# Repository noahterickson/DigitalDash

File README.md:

# DigitalDash

The digital dashboard project was completed by a group of students at Portland State University for the Electrical and Computer Engineering Capstone program on behalf of the Viking Motorsports team.

The digital dashboard is intended for a Formula SAE electric vehicle and functions as a visual display of information for various systems on the vehicle.

[Check out our wiki](https://github.com/noahterickson/DigitalDash/wiki)

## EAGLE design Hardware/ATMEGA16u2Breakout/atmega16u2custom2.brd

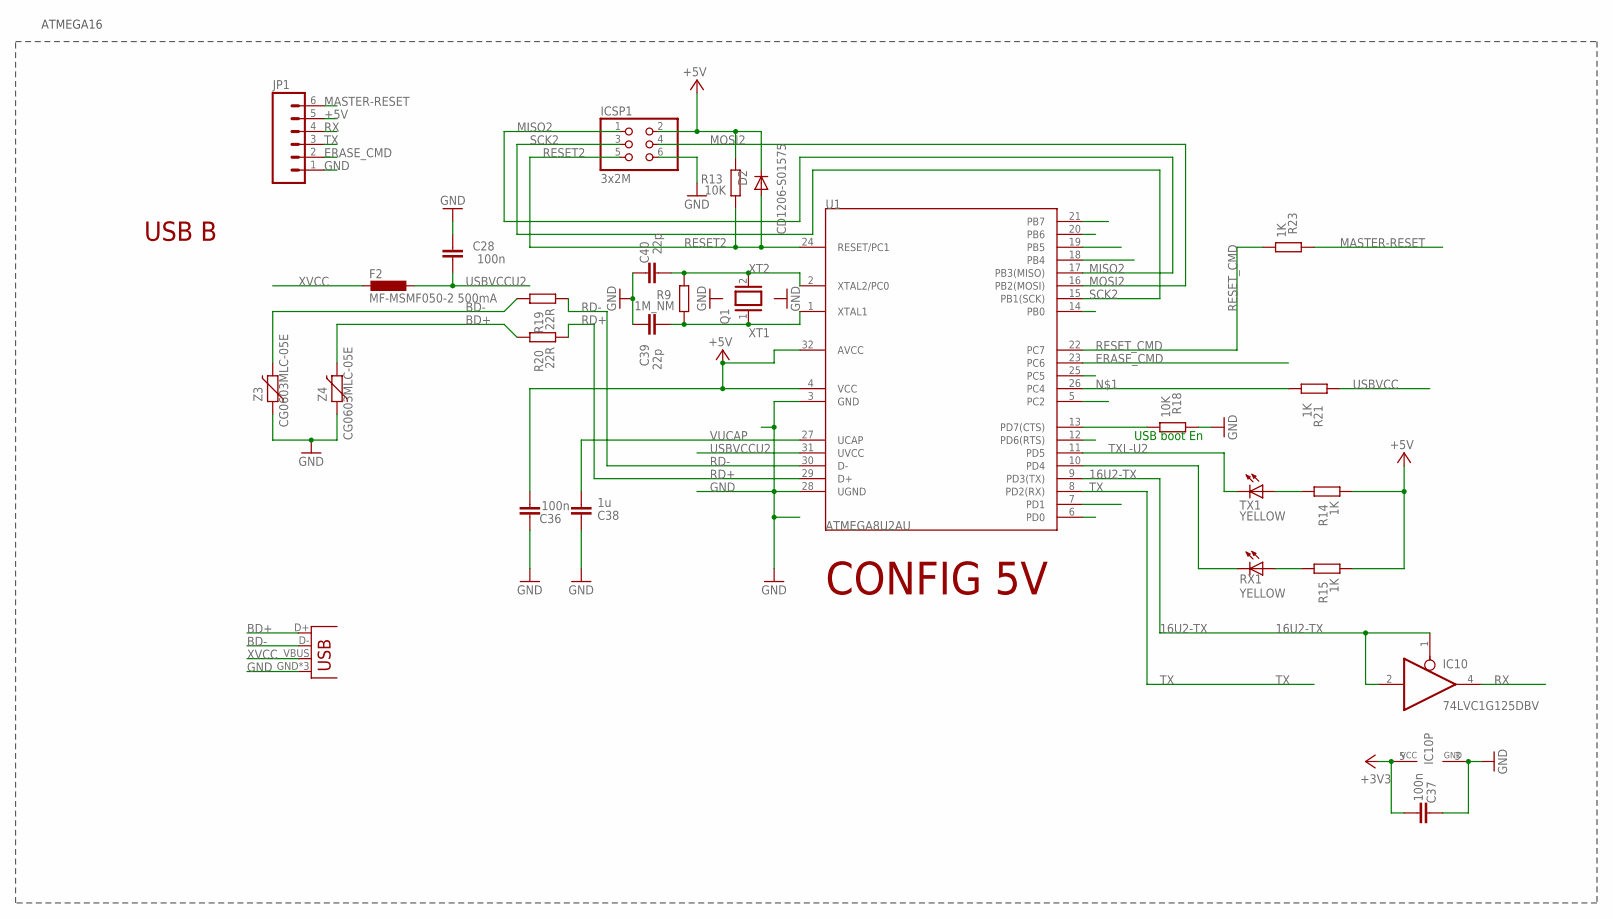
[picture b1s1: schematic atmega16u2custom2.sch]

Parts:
C28, C36, C37: 100n; C0805
C38: 1u; C0805
C39, C40: 22p; C0805
D2: CD1206-S01575; MINIMELF
F2: MF-MSMF050-2 500mA; L1812
IC10: 74LVC1G125DBV; SOT23-5
ICSP1: 3x2M; 2X03
JP1: M06NO_SILK; 1X06_NO_SILK
JP2: USB-MICROB
Q1: XTAL/S; QS
R9: 1M_NM; R0805
R13, R18: 10K; R0805
R14, R15, R21, R23: 1K; R0805
R19, R20: 22R; R0805
RX1: YELLOW; CHIP-LED0805
TX1: YELLOW; CHIP-LED0805
U1: ATMEGA8U2AU; TQFP32-08
Z3, Z4: CG0603MLC-05E; CT/CN0603

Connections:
8PB4: U1.18 (PB4)
8PB5: U1.19 (PB5)
8PB6: U1.20 (PB6)
16U2-TX: IC10.1 (OE), IC10.2 (I), U1.9 (PD3(TX))
+3V3: C37.1, IC10.5 (VCC)
+5V: C36.1, D2.C, ICSP1.2, JP1.5, R13.2, R14.1, R15.1, U1.4 (VCC), U1.32 (AVCC)
BD+: JP2.D+, R20.2, Z4.2
BD-: JP2.D-, R19.2, Z3.2
DTR: R18.1, U1.13 (PD7(CTS))
ERASE_CMD: JP1.2, U1.23 (PC6)
GND: C28.2, C36.2, C37.2, C38.2, C39.2, C40.2, IC10.3 (GND), ICSP1.6, JP1.1, JP2.GND, JP2.MT1 (GND), JP2.MT2 (GND), R18.2, U1.3 (GND), U1.28 (UGND), Z3.1, Z4.1
MASTER-RESET: JP1.6, R23.2
MISO2: ICSP1.1, U1.17 (PB3(MISO))
MOSI2: ICSP1.4, U1.16 (PB2(MOSI))
unnamed: R21.1, U1.26 (PC4)
unnamed: R15.2, RX1.A
unnamed: R14.2, TX1.A
RD+: R20.1, U1.29 (D+)
RD-: R19.1, U1.30 (D-)
RESET2: D2.A, ICSP1.5, R13.1, U1.24 (RESET/PC1)
RESET_CMD: R23.1, U1.22 (PC7)
RX: IC10.4 (O), JP1.4
RXL-U2: RX1.C, U1.10 (PD4)
SCK2: ICSP1.3, U1.15 (PB1(SCK))
TX: JP1.3, U1.8 (PD2(RX))
TXL-U2: TX1.C, U1.11 (PD5)
USBVCC: R21.2
USBVCCU2: C28.1, F2.1, U1.31 (UVCC)
VUCAP: C38.1, U1.27 (UCAP)
XT1: C39.1, Q1.1, R9.1, U1.1 (XTAL1)
XT2: C40.1, Q1.2, R9.2, U1.2 (XTAL2/PC0)
XVCC: F2.2, JP2.VBUS

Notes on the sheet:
USB boot En
CONFIG 5V
USB B
ATMEGA16

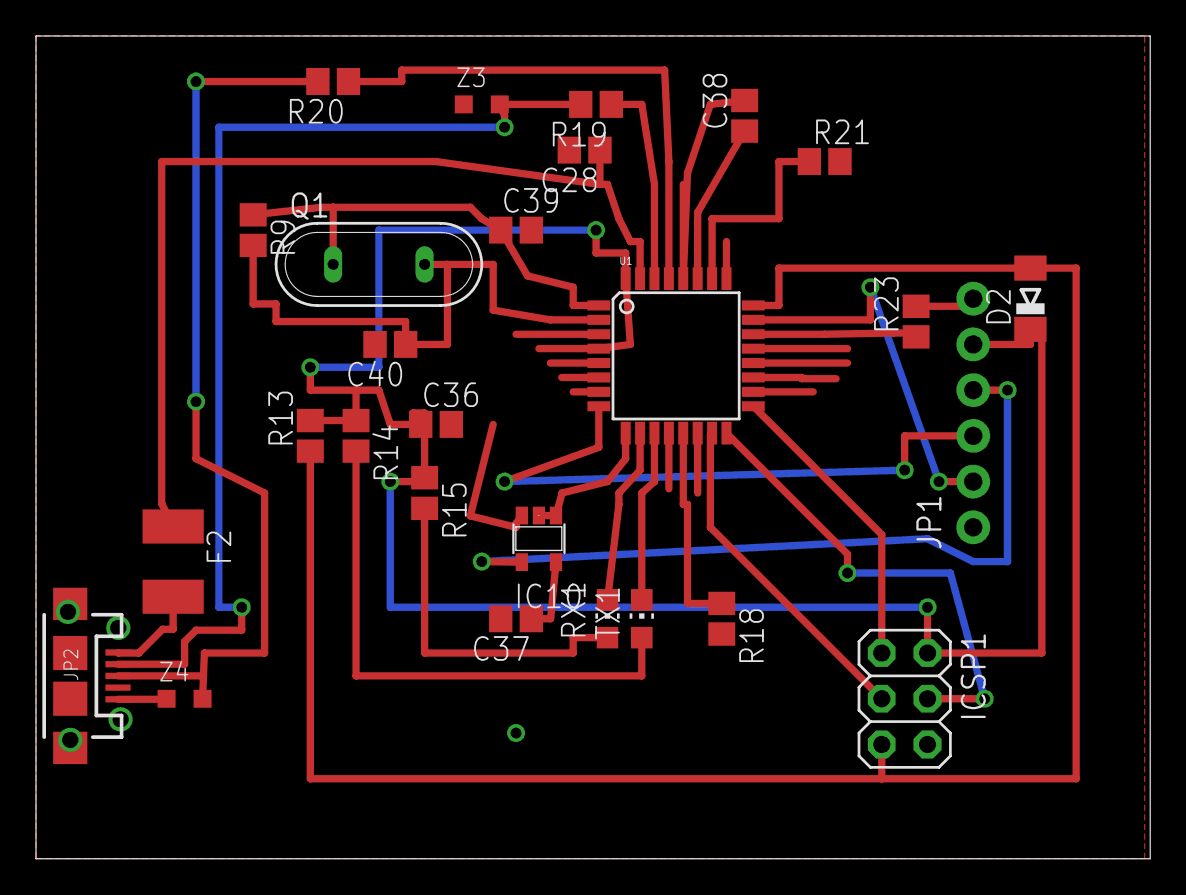
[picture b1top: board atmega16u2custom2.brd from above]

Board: 2 copper layers, 61.9 x 45.7 mm, 27 parts (0 on the bottom side), 28 nets.

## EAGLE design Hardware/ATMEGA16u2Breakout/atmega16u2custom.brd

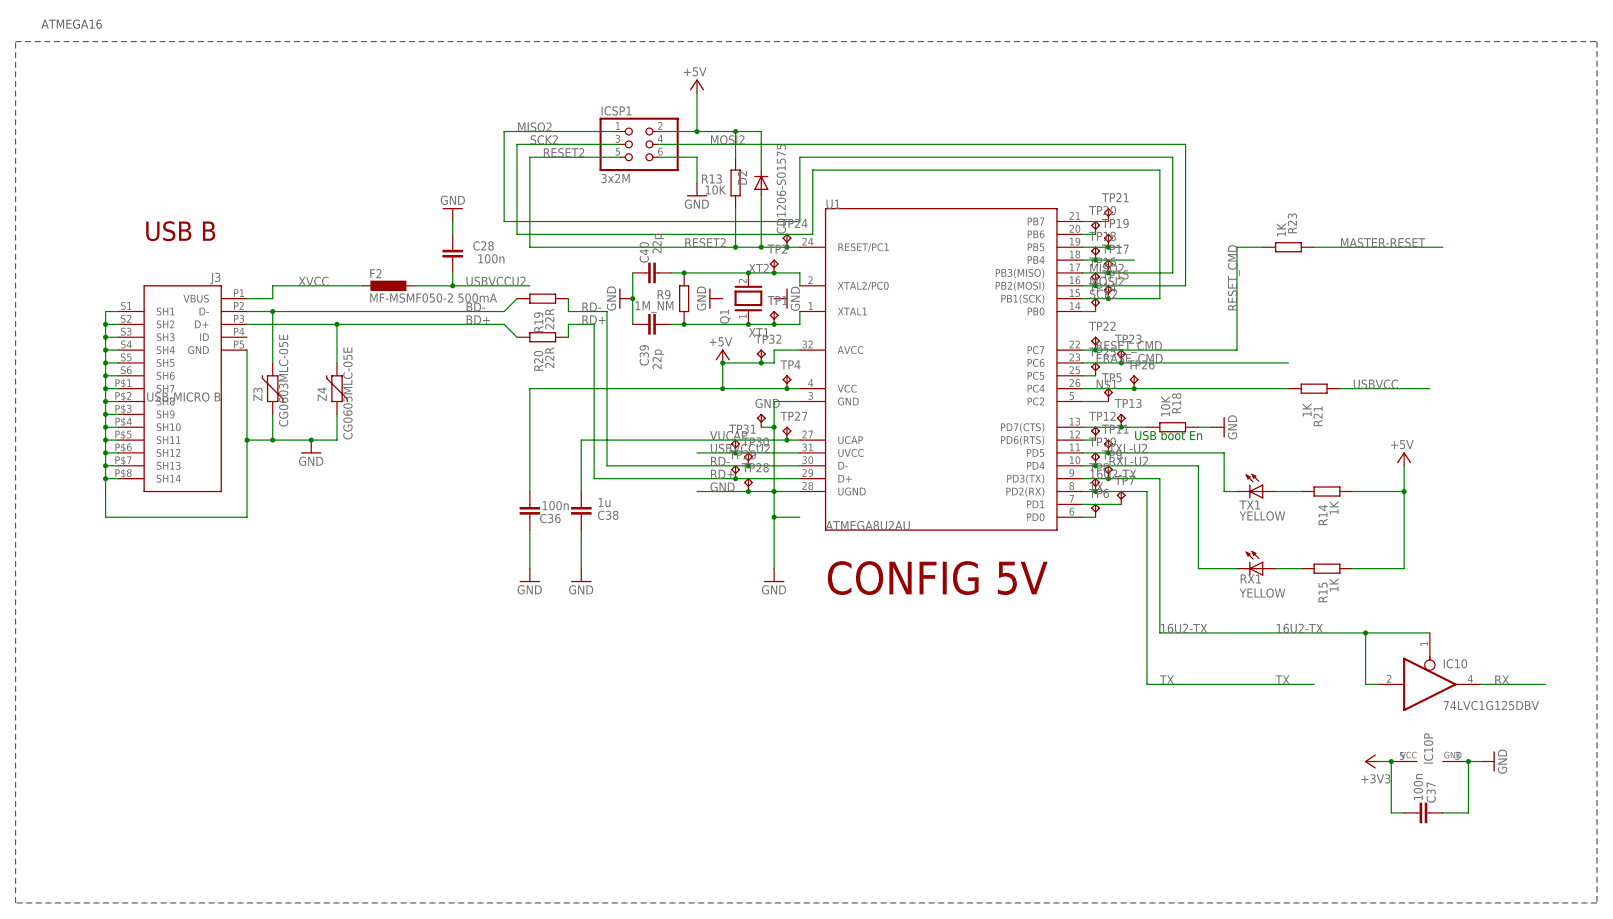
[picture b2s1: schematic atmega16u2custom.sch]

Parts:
C28, C36, C37: 100n; C0805
C38: 1u; C0805
C39, C40: 22p; C0805
D2: CD1206-S01575; MINIMELF
F2: MF-MSMF050-2 500mA; L1812
GND: TPB1,27; B1,27
IC10: 74LVC1G125DBV; SOT23-5
ICSP1: 3x2M; 2X03
J3: USB-MICRO B; CON2_USB_MICRO_B_AT
Q1: XTAL/S; QS
R9: 1M_NM; R0805
R13, R18: 10K; R0805
R14, R15, R21, R23: 1K; R0805
R19, R20: 22R; R0805
RX1: YELLOW; CHIP-LED0805
TP1, TP2, TP4, TP5, TP6, TP7, TP8, TP9, TP10, TP11, TP12, TP13, TP14, TP15, TP16, TP17, TP18, TP19, TP20, TP21, TP22, TP23, TP24, TP25, TP26, TP27, TP28, TP29, TP30, TP31, TP32: TPB1,27; B1,27
TX1: YELLOW; CHIP-LED0805
U1: ATMEGA8U2AU; TQFP32-08
Z3, Z4: CG0603MLC-05E; CT/CN0603

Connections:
8PB4: TP18.TP, U1.18 (PB4)
8PB5: TP19.TP, U1.19 (PB5)
8PB6: TP20.TP, U1.20 (PB6)
16U2-TX: IC10.1 (OE), IC10.2 (I), TP9.TP, U1.9 (PD3(TX))
+3V3: C37.1, IC10.5 (VCC)
+5V: C36.1, D2.C, ICSP1.2, R13.2, R14.1, R15.1, TP4.TP, TP32.TP, U1.4 (VCC), U1.32 (AVCC)
BD+: J3.P3 (D+), R20.2, Z4.2
BD-: J3.P2 (D-), R19.2, Z3.2
DTR: R18.1, TP13.TP, U1.13 (PD7(CTS))
ERASE_CMD: TP23.TP, U1.23 (PC6)
GND: C28.2, C36.2, C37.2, C38.2, C39.2, C40.2, GND.TP, IC10.3 (GND), ICSP1.6, J3.P5 (GND), J3.P$1 (SH7), J3.P$2 (SH8), J3.P$3 (SH9), J3.P$4 (SH10), J3.P$5 (SH11), J3.P$6 (SH12), J3.P$7 (SH13), J3.P$8 (SH14), J3.S1 (SH1), J3.S2 (SH2), J3.S3 (SH3), J3.S4 (SH4), J3.S5 (SH5), J3.S6 (SH6), R18.2, TP28.TP, U1.3 (GND), U1.28 (UGND), Z3.1, Z4.1
MASTER-RESET: R23.2
MISO2: ICSP1.1, TP17.TP, U1.17 (PB3(MISO))
MOSI2: ICSP1.4, TP16.TP, U1.16 (PB2(MOSI))
unnamed: R21.1, TP26.TP, U1.26 (PC4)
unnamed: TP5.TP, U1.5 (PC2)
unnamed: TP6.TP, U1.6 (PD0)
unnamed: R15.2, RX1.A
unnamed: TP7.TP, U1.7 (PD1)
unnamed: TP12.TP, U1.12 (PD6(RTS))
unnamed: TP25.TP, U1.25 (PC5)
unnamed: TP14.TP, U1.14 (PB0)
unnamed: TP21.TP, U1.21 (PB7)
unnamed: R14.2, TX1.A
RD+: R20.1, TP29.TP, U1.29 (D+)
RD-: R19.1, TP30.TP, U1.30 (D-)
RESET2: D2.A, ICSP1.5, R13.1, TP24.TP, U1.24 (RESET/PC1)
RESET_CMD: R23.1, TP22.TP, U1.22 (PC7)
RX: IC10.4 (O)
RXL-U2: RX1.C, TP10.TP, U1.10 (PD4)
SCK2: ICSP1.3, TP15.TP, U1.15 (PB1(SCK))
TX: TP8.TP, U1.8 (PD2(RX))
TXL-U2: TP11.TP, TX1.C, U1.11 (PD5)
USBVCC: R21.2
USBVCCU2: C28.1, F2.1, TP31.TP, U1.31 (UVCC)
VUCAP: C38.1, TP27.TP, U1.27 (UCAP)
XT1: C39.1, Q1.1, R9.1, TP1.TP, U1.1 (XTAL1)
XT2: C40.1, Q1.2, R9.2, TP2.TP, U1.2 (XTAL2/PC0)
XVCC: F2.2, J3.P1 (VBUS)

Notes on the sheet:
USB boot En
CONFIG 5V
USB B
ATMEGA16

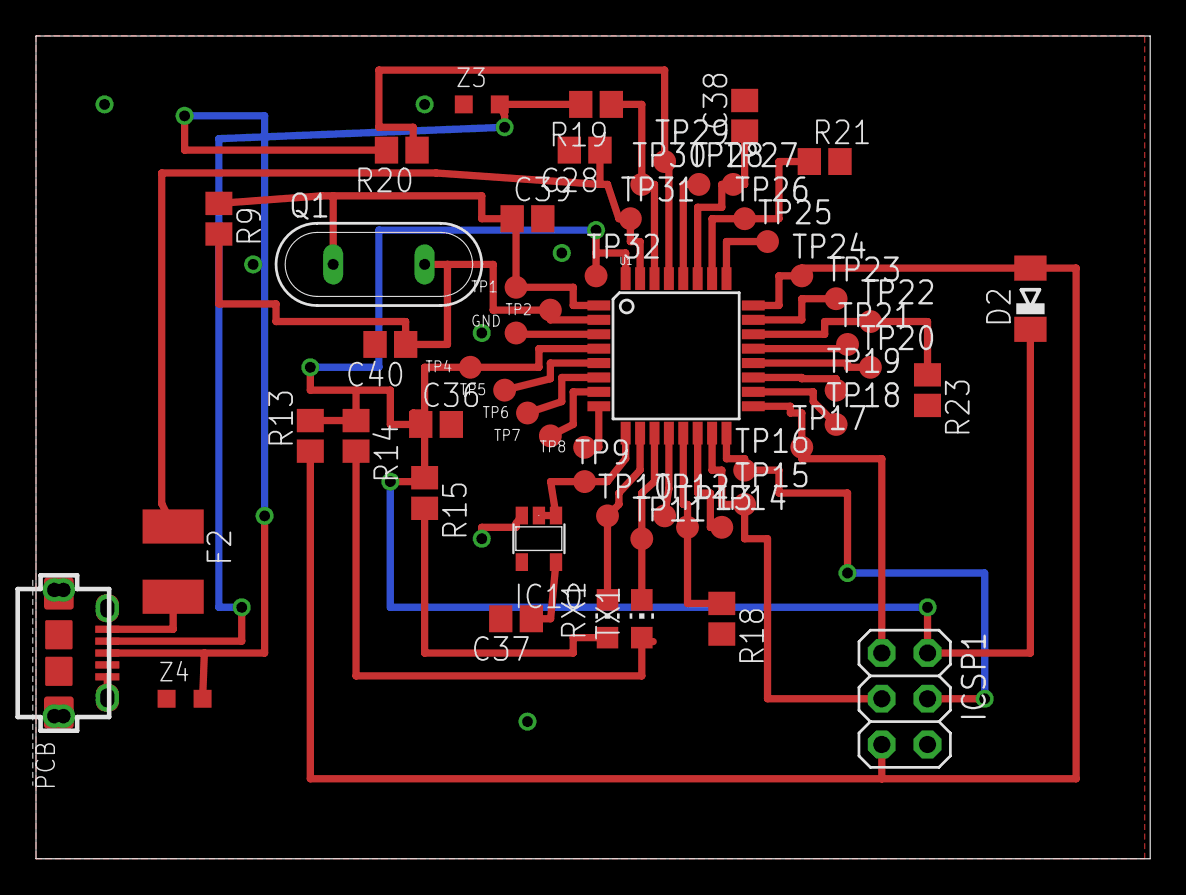
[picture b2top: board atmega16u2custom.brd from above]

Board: 2 copper layers, 61.9 x 45.7 mm, 58 parts (0 on the bottom side), 36 nets.

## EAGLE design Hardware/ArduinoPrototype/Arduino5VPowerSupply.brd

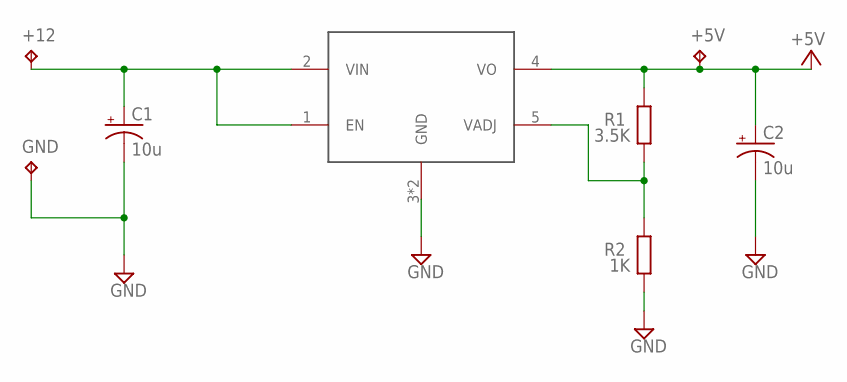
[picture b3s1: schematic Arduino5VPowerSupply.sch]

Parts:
+5V, +12: TPPAD1-13; P1-13
C1, C2: 10u; 153CLV-0405
GND: TPPAD1-13; P1-13
R1: 3.5K; R0805
R2: 1K; R0805
U5: TLF1963TBATMA1; DPAK

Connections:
+5V: +5V.TP, C2.+, R1.2, U5.4 (VO)
GND: C1.-, C2.-, GND.TP, R2.1, U5.3 (GND), U5.6 (GND)
unnamed: +12.TP, C1.+, U5.1 (EN), U5.2 (VIN)
unnamed: R1.1, R2.2, U5.5 (VADJ)

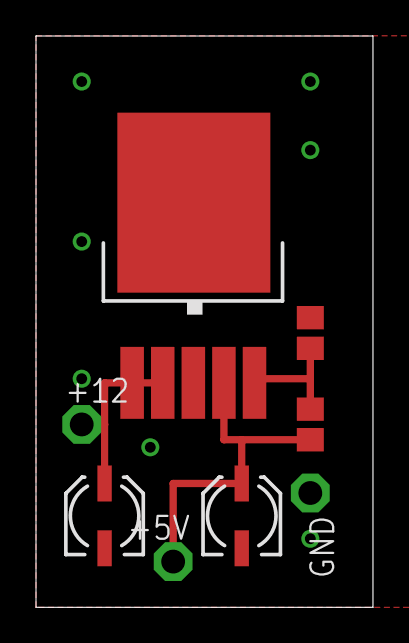
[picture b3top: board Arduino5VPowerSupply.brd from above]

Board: 2 copper layers, 18.7 x 31.7 mm, 8 parts (0 on the bottom side), 4 nets.

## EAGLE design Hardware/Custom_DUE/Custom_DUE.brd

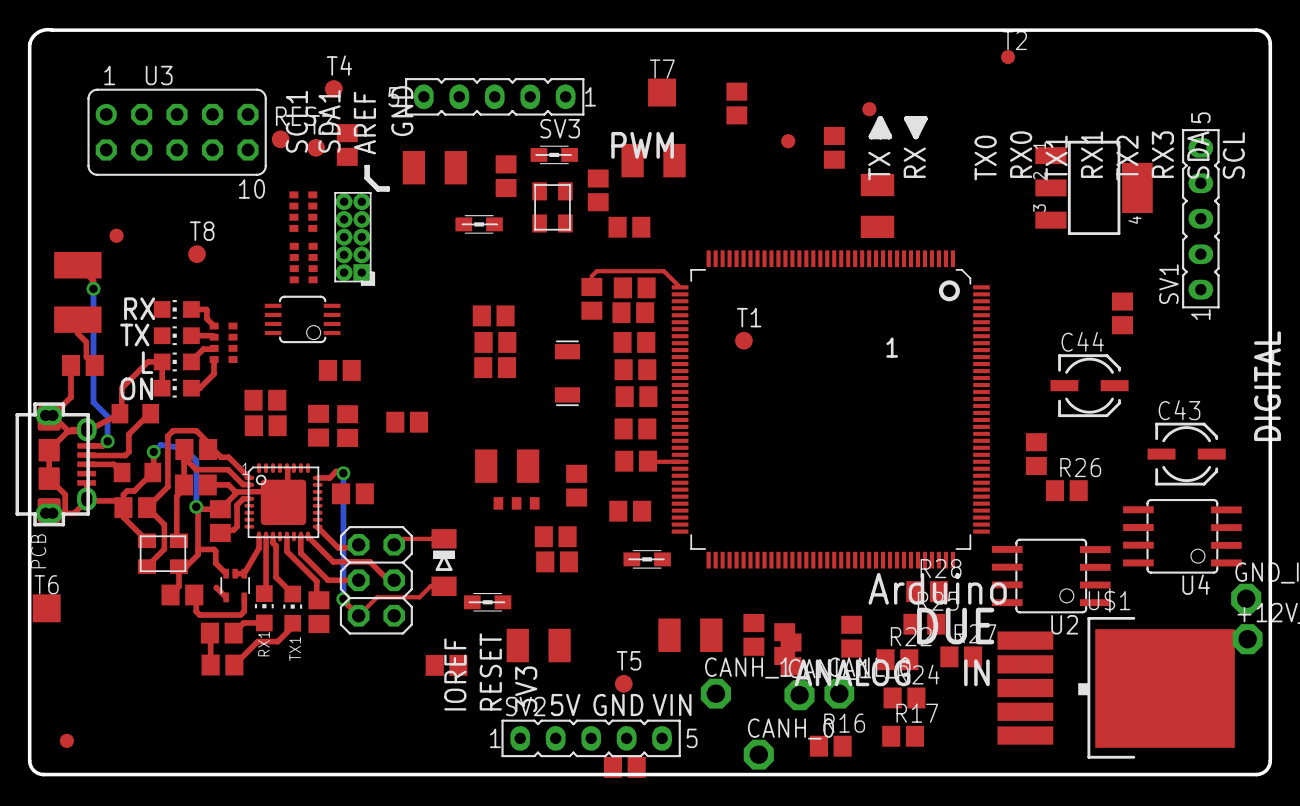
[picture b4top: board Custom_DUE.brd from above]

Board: 2 copper layers, 88.9 x 53.4 mm, 116 parts (0 on the bottom side), 80 nets.

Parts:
+12V_IN: TPPAD1-13; P1-13
BR1: NM; J0402
C1, C2, C3, C11, C29, C33: 10u; SMC_B
C4, C5, C6, C7, C8, C9, C10, C12, C13, C14, C15, C16, C17, C18, C19, C28, C30, C32, C34, C36, C37: 100n; C0805
C21, C22, C25, C39, C40: 22p; C0805
C23, C24: 22pF_NM; C0805
C38: 1u; C0805
C43, C44: 10u; 153CLV-0405
CANH_0, CANH_1: TPPAD1-13; P1-13
CANL_0, CANL_1: TPPAD1-13; P1-13
D2: CD1206-S01575; MINIMELF
F2: MF-MSMF050-2 500mA; L1812
FID1, FID2, FID3, FID4: FIDUCIALMOUNT; FIDUCIA-MOUNT
GND_IN: TPPAD1-13; P1-13
IC1: LMV358IDGKR; MSOP08
IC4: NCP1117ST33T3G -3V3; SOT223
IC6: ATMEGA16U2-MU; MLF32
IC10: 74LVC1G125DCK; SC70-5
ICSP1: 3x2M; 2X03
J3: USB-MICRO B; CON2_USB_MICRO_B_AT
JR1: 0R; R0805
JTAG: PINHEAD_2X05_127
L: YELLOW; CHIP-LED0805
L1, L2, L3, L5: MH2029-300Y; 0805
ON: GREEN; CHIP-LED0805
R1: 0R; R0805
R4: 100K; R0805
R5, R6: 39R 1%; R0805
R7: 6k8 1%; R0805
R8: 0R_NM; R0805
R9: 1M_NM; R0805
R13, R18: 10K; R0805
R14, R15, R17, R21, R23: 1K; R0805
R16: 3.5K; R0805
R19, R20: 22R; R0805
R22, R24, R26, R27: 50; R0805
R25, R28: 120; R0805
RES: TPB1,27; B1,27
RN1, RN2: 100K; CAT16
RN3: 1k; CAY16
RX, RX1: YELLOW; CHIP-LED0805
SV1, SV2, SV3: FE05-1
T1, T3, T4, T5, T8: TPB1,27; B1,27
T2: TPTP10R; TP10R
T6, T7: TPTP20SQ; TP20SQ
TX, TX1: YELLOW; CHIP-LED0805
U1: ATSAM3X8EA-AU; LQFP144
U2, U4: MCP2551; SOIC8
U3: LCD_DISPLAY; FE05-2
U$1: TLF1963TBATMA1; DPAK
Y1: 12MHz KX-7 20pF; CRYSTAL-3.2-2.5
Y2: 32.768Khz; RESONATOR_EPSON_FC_145
Y4: 16MHz KX-7 20pF; CRYSTAL-3.2-2.5
Z3, Z4: CG0603MLC-05E; CT/CN0805

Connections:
16U2-TX: IC6.9, IC10.1, IC10.2
+3V3: BR1.3, C1.+, C4.2, C5.2, C6.2, C7.2, C8.2, C18.2, C29.+, C37.1, IC4.2, IC4.4, IC10.5, JR1.1, JTAG.1, L1.1, L2.1, R4.2, RN1.5, RN1.6, RN2.2, RN2.3, RN3.5, RN3.7, RN3.8, SV3.4, T2.TP, T3.TP, U1.11, U1.52, U1.57, U1.62, U1.105, U1.125
+5V: C30.2, C36.1, C44.+, D2.C, IC1.8, IC4.3, IC6.4, IC6.32, ICSP1.2, R13.2, R14.1, R15.1, R16.2, R22.2, R27.2, SV3.5, T4.TP, T8.TP, U2.3, U3.1, U3.10, U4.3, U$1.4
AD0: SV2.5, U1.78
AD1: SV2.4, U1.79
AD2: SV2.3, U1.80
AVREF: C19.2, L3.2, U1.75
AVREFL: BR1.2, C34.2, JR1.2, L3.1
BD+: J3.P3, R20.2, Z4.2
BD-: J3.P2, R19.2, Z3.2
CANRX0: U1.24, U4.4
CANTX0: U1.23, U4.1
CANTX1/IO: U1.140, U2.1
D+: R6.1, U1.37
D-: R5.1, U1.38
DAC0(CANRX1): U1.76, U2.4
DAC1: SV2.1, U1.77
DTR: IC6.13, R18.1
GND: C1.-, C2.-, C3.-, C4.1, C5.1, C6.1, C7.1, C8.1, C9.1, C10.1, C11.-, C12.1, C13.1, C14.1, C15.1, C16.1, C17.1, C18.1, C19.1, C21.2, C22.2, C23.2, C24.2, C25.2, C28.2, C29.-, C30.1, C32.1, C33.-, C34.1, C36.2, C37.2, C38.2, C39.2, C40.2, C43.-, C44.-, GND_IN.TP, IC1.4, IC4.1, IC6.3, IC6.28, IC6.33, IC10.3, ICSP1.6, J3.P5, J3.P$1, J3.P$2, J3.P$3, J3.P$4, J3.P$5, J3.P$6, J3.P$7, J3.P$8, J3.S1, J3.S2, J3.S3, J3.S4, J3.S5, J3.S6, JTAG.3, JTAG.5, JTAG.9, L.C, ON.C, R7.1, R8.1, R17.1, R18.2, R24.1, R26.1, RN1.1, RN1.2, RN1.7, RN1.8, RN2.1, RN2.4, RN2.5, RN2.8, SV3.1, SV3.2, T5.TP, T6.TP, T7.TP, U1.12, U1.33, U1.44, U1.46, U1.54, U1.58, U1.74, U1.106, U1.126, U2.2, U2.8, U3.4, U3.7, U4.2, U4.8, U$1.3, U$1.6, Y1.2, Y1.4, Y4.2, Y4.4, Z3.1, Z4.1
JTAG_RESET: JTAG.10, R1.1, RN1.4
JTAG_TCK: JTAG.4, RN2.7, U1.28
JTAG_TDI: JTAG.8, RN1.3, U1.29
JTAG_TDO: JTAG.6, U1.30
JTAG_TMS: JTAG.2, RN2.6, U1.31
L13: IC1.1, IC1.2, RN3.6
MASTER-RESET: R1.2, R23.2, T1.TP, U1.47
MISO2: IC6.17, ICSP1.1
MOSI2: IC6.16, ICSP1.4
unnamed: IC6.26, R21.1
unnamed: L.A, RN3.3
unnamed: ON.A, RN3.4
unnamed: R15.2, RX1.A
unnamed: R8.2, U1.51
unnamed: R4.1, U1.53
unnamed: R5.2, U1.43
unnamed: R6.2, U1.42
unnamed: +12V_IN.TP, C43.+, U$1.1, U$1.2
unnamed: R14.2, TX1.A
unnamed: R16.1, R17.2, U$1.5
unnamed: R26.2, R27.1, U2.5
unnamed: R22.1, R24.2, U4.5
unnamed: CANH_0.TP, R25.2, U4.7
unnamed: CANL_0.TP, R25.1, U4.6
unnamed: RES.TP, U3.2, U3.9
unnamed: CANH_1.TP, R28.2, U2.7
unnamed: CANL_1.TP, R28.1, U2.6
unnamed: RN3.1, RX.A
unnamed: RN3.2, TX.A
PWM2: SV1.5, U1.144
PWM3: SV1.4, U1.139
PWM5: SV1.2, U1.136
PWM6: SV1.1, U1.135
PWM13: IC1.3, U1.68
RD+: IC6.29, R20.1
RD-: IC6.30, R19.1
RESET2: D2.A, IC6.24, ICSP1.5, R13.1
RESET_CMD: IC6.22, R23.1
RX: IC10.4, U1.27, U3.5, U3.6
RXL: RX.C, U1.103
RXL-U2: IC6.10, RX1.C
SCK2: IC6.15, ICSP1.3
SS0/PWM10: U1.102, U1.111
SS1/PWM4: SV1.3, U1.112, U1.137
TX: IC6.8, U1.2, U3.3, U3.8
TXL: TX.C, U1.107
TXL-U2: IC6.11, TX1.C
USBVCCU2: C28.1, F2.1, IC6.31
VBG: C25.1, R7.2, U1.40
VDDANA: C3.+, C10.2, L1.2, U1.73
VDDOUT: C11.+, C12.2, C13.2, C14.2, C15.2, C16.2, C17.2, L5.1, U1.10, U1.45, U1.56, U1.61, U1.104, U1.124
VDDOUTMI: C2.+, C9.2, L2.2, U1.41
VDDPLL: C32.2, C33.+, L5.2, U1.34
VUCAP: C38.1, IC6.27
XIN: C22.1, U1.36, Y1.1
XIN32: C24.1, U1.48, Y2.P$2
XOUT: C21.1, U1.35, Y1.3
XOUT32: C23.1, U1.49, Y2.P$1
XT1: C39.1, IC6.1, R9.1, Y4.1
XT2: C40.1, IC6.2, R9.2, Y4.3
XVCC: F2.2, J3.P1

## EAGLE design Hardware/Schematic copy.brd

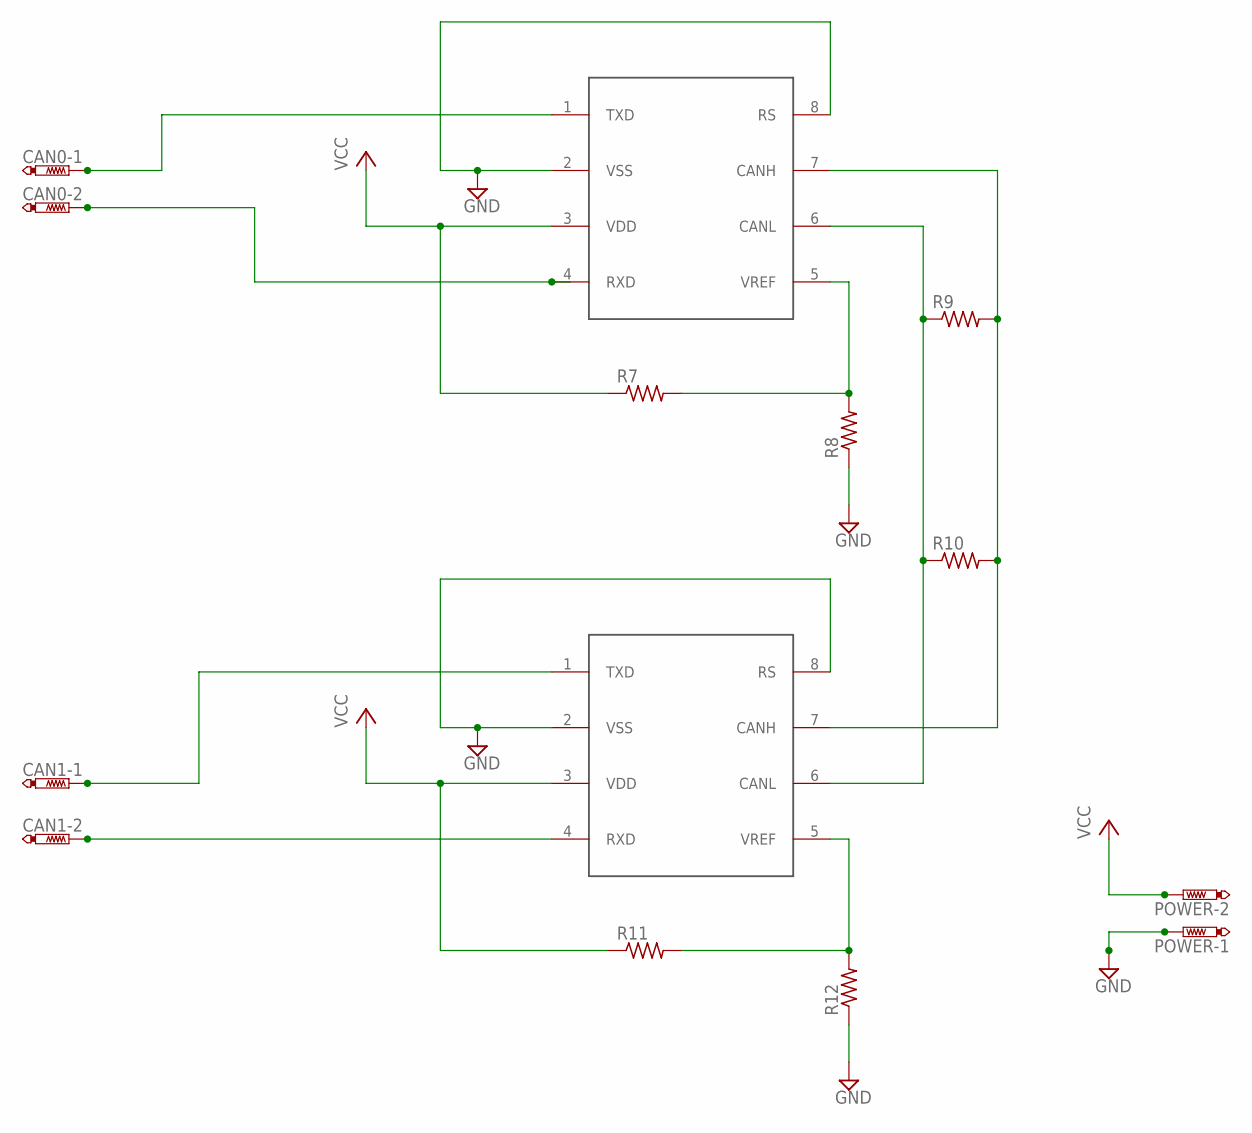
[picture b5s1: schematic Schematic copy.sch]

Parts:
CAN0, CAN1: PTR2; P2-38-17
POWER: PTR2; P2-38-17
R7, R8, R9, R10, R11, R12: R-US_0204/5; 0204/5
U$2, U$3: MCP2551-DIP; DIL08

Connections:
CH: R9.2, R10.2, U$2.7 (CANH), U$3.7 (CANH)
CL: R9.1, R10.1, U$2.6 (CANL), U$3.6 (CANL)
GND: POWER.TP-1, R8.1, R12.1, U$2.2 (VSS), U$2.8 (RS), U$3.2 (VSS), U$3.8 (RS)
unnamed: R7.2, R8.2, U$2.5 (VREF)
unnamed: R11.2, R12.2, U$3.5 (VREF)
RX1: CAN0.TP-2, U$2.4 (RXD)
RX2: CAN1.TP-2, U$3.4 (RXD)
TX1: CAN0.TP-1, U$2.1 (TXD)
TX2: CAN1.TP-1, U$3.1 (TXD)
VCC: POWER.TP-2, R7.1, R11.1, U$2.3 (VDD), U$3.3 (VDD)

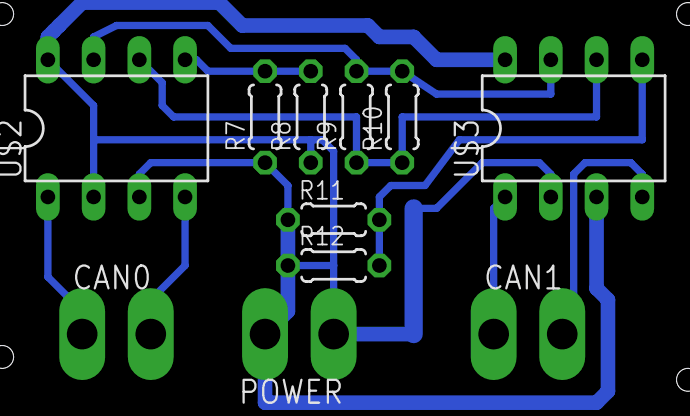
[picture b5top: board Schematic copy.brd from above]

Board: 2 copper layers, 11 parts (0 on the bottom side), 10 nets.

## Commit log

2014-12-01 Documentation
2014-12-01 Grading
2014-12-17 Added datasheets for the research I have done so far.
2014-12-23 Added directory for weekly meeting presentations
2014-12-28 jaime
2015-01-04 Project Proposal
2015-01-04 Wiki topbar
2015-01-04 Cleanup
2015-01-04 Cleanup2
2015-01-04 Requirements
2015-01-04 Proposal Update
2015-01-05 Project Schedule
2015-01-17 Design Prototype A
    Prototype of mounting the screen
2015-01-17 Added meeting presentation
2015-01-17 Proposal Powerpoint
2015-01-20 Car Pictures
    Pictures taken of the car, to see where the screen can be placed
2015-01-20 GUI Display example
    Example of how the display may look
2015-01-20 Updated
    This is not the final copy, times for the timeline line section of the
    presentation
2015-01-20 updated proposal
2015-01-21 Added dates to project proposal
2015-01-21 updated
    updated
2015-01-21 Added microproc and transceiver tables
2015-01-21 Noah's Slides
2015-01-21 noahs slides again in ppt
2015-01-21 Added project requirement slides
2015-01-21 Final Updated Version on Proposal
2015-01-22 FINAL PROJECT FINALLY
2015-01-24 Project Proposal Update
2015-01-25 Meeting 3 added
2015-01-25 Initial 12815 meeting
2015-01-25 Added the due_can library and added some test code for polling and interrupt driven CAN messaging
2015-01-25 Meeting 3 & Project Proposal
2015-01-26 New Project Schedule Uploaded
    Updated
2015-01-26 deleted old project schedule
2015-01-26 New Schedule Uploaded
    Spelling corrections
2015-01-27 Bill of Material Documentation
    List of parts ordered to date.
2015-01-27 Small changes to proposal
2015-01-28 Prices for components updated
    added unit price for due and tranceivers plus shipping
2015-01-28 Update
    completion % update
2015-01-28 Update
    Format
2015-01-28 New Motivation section
2015-01-28 Proposal document for meetings, success, and roadblocks
2015-01-31 PDF Version of the Project Schedule
2015-01-31 Remove uneeded data sheet
2015-01-31 Arduino Due Schematic
2015-01-31 Gui image
2015-01-31 fhghggh
2015-01-31 block diagram
2015-01-31 Added datasheet for RMS CAN
2015-01-31 Skeleton code for final software
2015-01-31 BMS Can programming
    document of can messages from bms
2015-01-31 COMMIT 64
2015-01-31 Commit 65
2015-01-31 all the commits 66
2015-01-31 CAN datasheet table document
2015-01-31 Schematic
2015-02-01 Test Plan
    Test plan update as needed
2015-02-01 Presentation slides for 2/4/2015
2015-02-01 Test plan pdf
    uploaded pdf version as per noah request
2015-02-03 Added schedule pictures
2015-02-03 Update
    Progress Update
2015-02-07 Update
    Added 'Poster Presentation Part'
2015-02-07 All PM100 CAN messages implemented
2015-02-07 Seperated software into multiple files
2015-02-07 Added BMS CAN messages to CAN1
2015-02-07 Update
    BOM updated
2015-02-10 Tests for CAN0 messages are added
2015-02-11 CAN1(BMS) tests added. Big endian conversion working correctly now. BMS values outputting correctly
2015-02-11 cxzbnvnbm,
2015-02-13 Prototype Board & Schematic
    This is the updated board and schematic for the prototype
2015-02-13 Progress Update
2015-02-19 test commit please ignore
    test commit please ignore
2015-02-20 Schedule Update
2015-02-22 Slides from weekly capstone meeting
2015-02-22 Debug prints that work with interrupts
2015-02-27 4D Screen images
2015-02-27 4D screen programming help
2015-02-28 Wiring Diagram
2015-02-28 Fancy Update
2015-02-28 Genie code added for screen
2015-03-02 Commit 100!
    Commit 100! Complete with weekly update presentation, some directory
    reorganization and report outline!
2015-03-03 Schedule Update
    Percent completed updated
2015-03-03 Weekly meeting slides
    Updated the slides for the weekly meeting.
2015-03-07 Screen code working
2015-03-07 Slides for the 3/11 weekly meeting
2015-03-14 jaime
    jhjhj
2015-03-14 Enclosure Design
    Some prototype designs for the enclosure
2015-03-14 BMS code now working. All values displayed to screen
2015-03-14 Jaime
    Board
2015-03-16 Update Schedule
    Updated percents project has been completed
2015-03-16 organized folders
    placed in a new folder
2015-03-21 Added function headers, removed test functions, and added some comments
2015-03-21 Bill of materials added to hardware
2015-03-21 Reorg
2015-03-21 Added defines for CAN message data
2015-03-21 BOM update
2015-03-21 RMS warning messages work and RMS symbol changes red on error
2015-03-25 Project Schedule Update
    Schedule Update
2015-03-31 Arduino power supply and basic enclosure
2015-04-05 Added pictures of prototype
2015-04-05 Resize pictures
2015-04-07 Hardware reorganization
2015-04-07 Hardware Reorg2
2015-04-07 Schematic cleanup for Jaime
2015-04-11 Schematic Update
2015-04-11 Reimbursement form
2015-04-11 Update on progress
2015-04-11 Rough code for demo program
2015-04-11 New Pictures
    BMS removed pictures
2015-04-11 Enclosure Added
2015-04-11 Complete demo program that compiles but is untested
2015-04-13 Remove event handler from main
2015-04-13 RMS state text strings added
2015-04-18 41515 meeting slides added
2015-04-18 Added slides for Justin
2015-04-18 eh
    crap
2015-04-18 Small debug stuff added to demo sender
2015-04-21 Added some old meeting slides
2015-04-21 VMS meeting demo slides updated
2015-04-21 Cleaned up thumbs.db and ds.store
2015-04-21 Added more old meeting slides
2015-04-21 new demo sender code for pots and refactored the main code some
2015-04-21 Added poster template
2015-04-23 Poster update
2015-04-25 Poster Update
    Update
2015-04-25 Update Again
    Update
2015-04-25 Mission critical pictures
2015-04-25 Sending motor temp to screen with EVCU
2015-04-25 gate driver temp working with demo
2015-04-25 Fairly close to working completely with demo program
2015-04-27 board pic uploaded
2015-04-28 Poster Updatesss
2015-04-28 Project Schedule Update
    Update
2015-04-28 Meeting slides and pictures added
2015-04-29 Support for motor torque added into Demo sender
2015-05-02 Receipts and poster update
2015-05-02 Reimbursements and Receipts
    The title says it all....
2015-05-02 Added RMS state messages to the screen
2015-05-04 Rough outline of my slides for Wednesday
2015-05-04 Final version of slides for 5/6
2015-05-05 Project Proposal Slides
2015-05-05 Code that has motor_torque not working
2015-05-05 PROPOSAL SLIDE FIXEDDDDDD
2015-05-05 Project Proposal Slides
    Now it's working NOAH!!
2015-05-05 Atmega16u2 Breakout board upload
2015-05-05 atmega16u2 breakout board update
2015-05-09 Motor torque, gate driver temperature and IMD now work on the demo program/screen.
2015-05-09 ATMEGA16u2 Board Update
2015-05-09 The battery guage now works on the screen and in the demo. The current version of the demo should be totally done
2015-05-09 Added comments and cleaned up the digital dash code
2015-05-09 Added some comments to the demo program
2015-05-11 Created a user manual for the screen. Pictures and some addiontal cleanup will be needed but it is a good start.
2015-05-12 Added weekly progress slides
2015-05-16 Poster update, COMMIT 199!!!
2015-05-16 commit 200, important picture added
2015-05-19 Schedule Update
    Update
2015-05-19 Final_Board_with_components pictures
    Picture
2015-05-19 Poster template levelled up to poster
2015-05-19 Its dangerous to go alone, take this poster upate
2015-05-19 Thank you, but our poster update is in another castle!
2015-05-19 All your poster updates are belong to us.
2015-05-20 Somebody set up us the poster updates
2015-05-20 Updated atmega16 breakout board, and gerbers
2015-05-22 Are you a bad enough poster update?
2015-05-23 The right poster updates in the wrong place can make all the difference in the world.
2015-05-23 You must update additional posters.
2015-05-23 Its a trap!!!! poster update
2015-05-23 You have died of poster updates.
2015-05-23 Do a poster update!
2015-05-23 Giant enemy crab
2015-05-23 Poster update has been defused.
2015-05-23 Poster updates for the poster updates throne!
2015-05-26 Receipt update
    update
2015-05-26 BMS warning messages now make BMS symbol turn red.
2015-05-26 Fixed issue with screen locking up related to the battery. Also changed scale of the motor torque input values
2015-05-26 Urist McEnclosurePicture
2015-05-26 A picture has been updated!
2015-05-26 GUI Screen Pictures
    Updated version of the GUI Screen
2015-05-26 Digital Dash Report Draft
    First Draft of the report
2015-05-27 Final Poster
    This is the copy of the final poster; Old versions has been moved into
    its own folder
2015-05-27 You're the Final Poster Harry!
    Final Version of the Final Poster Finally Poster
2015-05-28 Initial presentation upload
2015-05-28 File Reorganization and report update
2015-05-28 File reorg 2
2015-05-28 Report update
2015-05-28 presentation update
2015-05-29 Digital Dash GUI
    Files and images used to create GUI for Digital Dash
2015-06-01 Added pictures to the user manual
2015-06-01 Readme test, ignore
2015-06-01 Readme test again ignore
2015-06-01 Readme updated again, this is annoying
2015-06-01 Picture update
2015-06-02 Update the demo sender program to the newest version
2015-06-02 PIcture updatesss
2015-06-02 Changes to the presentation
2015-06-02 Changed the names of the software to better reflect what they do
2015-06-02 Final Presentation Update
2015-06-02 Final presentation upload forever
2015-06-02 Update names and remove motor temp from demo
2015-06-03 System Block Diagram
    Updated block diagram
2015-06-03 Inital commit of the polling code
2015-06-03 Weekly meeting slide and picture update
2015-06-03 Remove polling code that does not work
2015-06-03 Slides for weekly meeting
    slides for 5/20/15
2015-06-03 Updates library
    Included 4d system arduino library
2015-06-03 Readme update
    Added document on where to find most recent version of the library
2015-06-03 Slide updates
2015-06-03 Due and bare custom board
    Show difference in size between DUE and custom board
2015-06-03 test
2015-06-03 Version of genieArduino Library used
    Library for 4dsystem screen to work with arduino
2015-06-03 Updated read me file
    Provides link to most recent version of Due Can library
2015-06-03 Final presentation update
    Added to the conclusion
2015-06-03 updated presentation
    added to the conclusion
2015-06-03 Added system images
    uploaded project images of system components and testing diagram
2015-06-04 IMD working on the screen and junk code removed from the demo program.
    Choke on Noah
2015-06-04 Final code cleanup before we adjust scaling on the demo
2015-06-04 Presentation and BOM update
2015-06-05 Final version of the screen code with RMS states included
2015-06-05 Made final revisions to board
    added +5V and GND terminals for wire harness,
    fixed minor issues
2015-06-05 Demounit picture
2015-06-10 Capstone Report Draft Update
    Draft for the report has been updated
2015-06-10 Project Schedule Update
    Documentation & Testing for final implementation left.
2015-06-10 Word version of final report
2015-06-10 Latest report
2015-06-10 Integration Pictures Added
2015-06-10 limited space
2015-06-10 Enclosure picture
    Updated enclosure picture
2015-06-10 Deutsch Connector Pinout Picture
2015-06-10 Report revision 2
2015-06-10 Added a single r to the word "erros" in the report
2015-06-11 Final report
2015-06-11 Added drawings for enclosure and dash
2015-06-12 Add additional LED for warning state and add motor temp object to info screen
2015-06-12 Change LED type
2015-06-12 final software revision
2015-06-13 updated gui
    added motor temp and added led to blink fault state
2015-06-13 final revision of gui
    updated guid to included motor torque and fixed the bms error

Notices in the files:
parts and their libraries:
SparkFun-DigitalIC: Licensing: Creative Commons ShareAlike 4.0 International - https://creativecommons.org/licenses/by-sa/4.0
